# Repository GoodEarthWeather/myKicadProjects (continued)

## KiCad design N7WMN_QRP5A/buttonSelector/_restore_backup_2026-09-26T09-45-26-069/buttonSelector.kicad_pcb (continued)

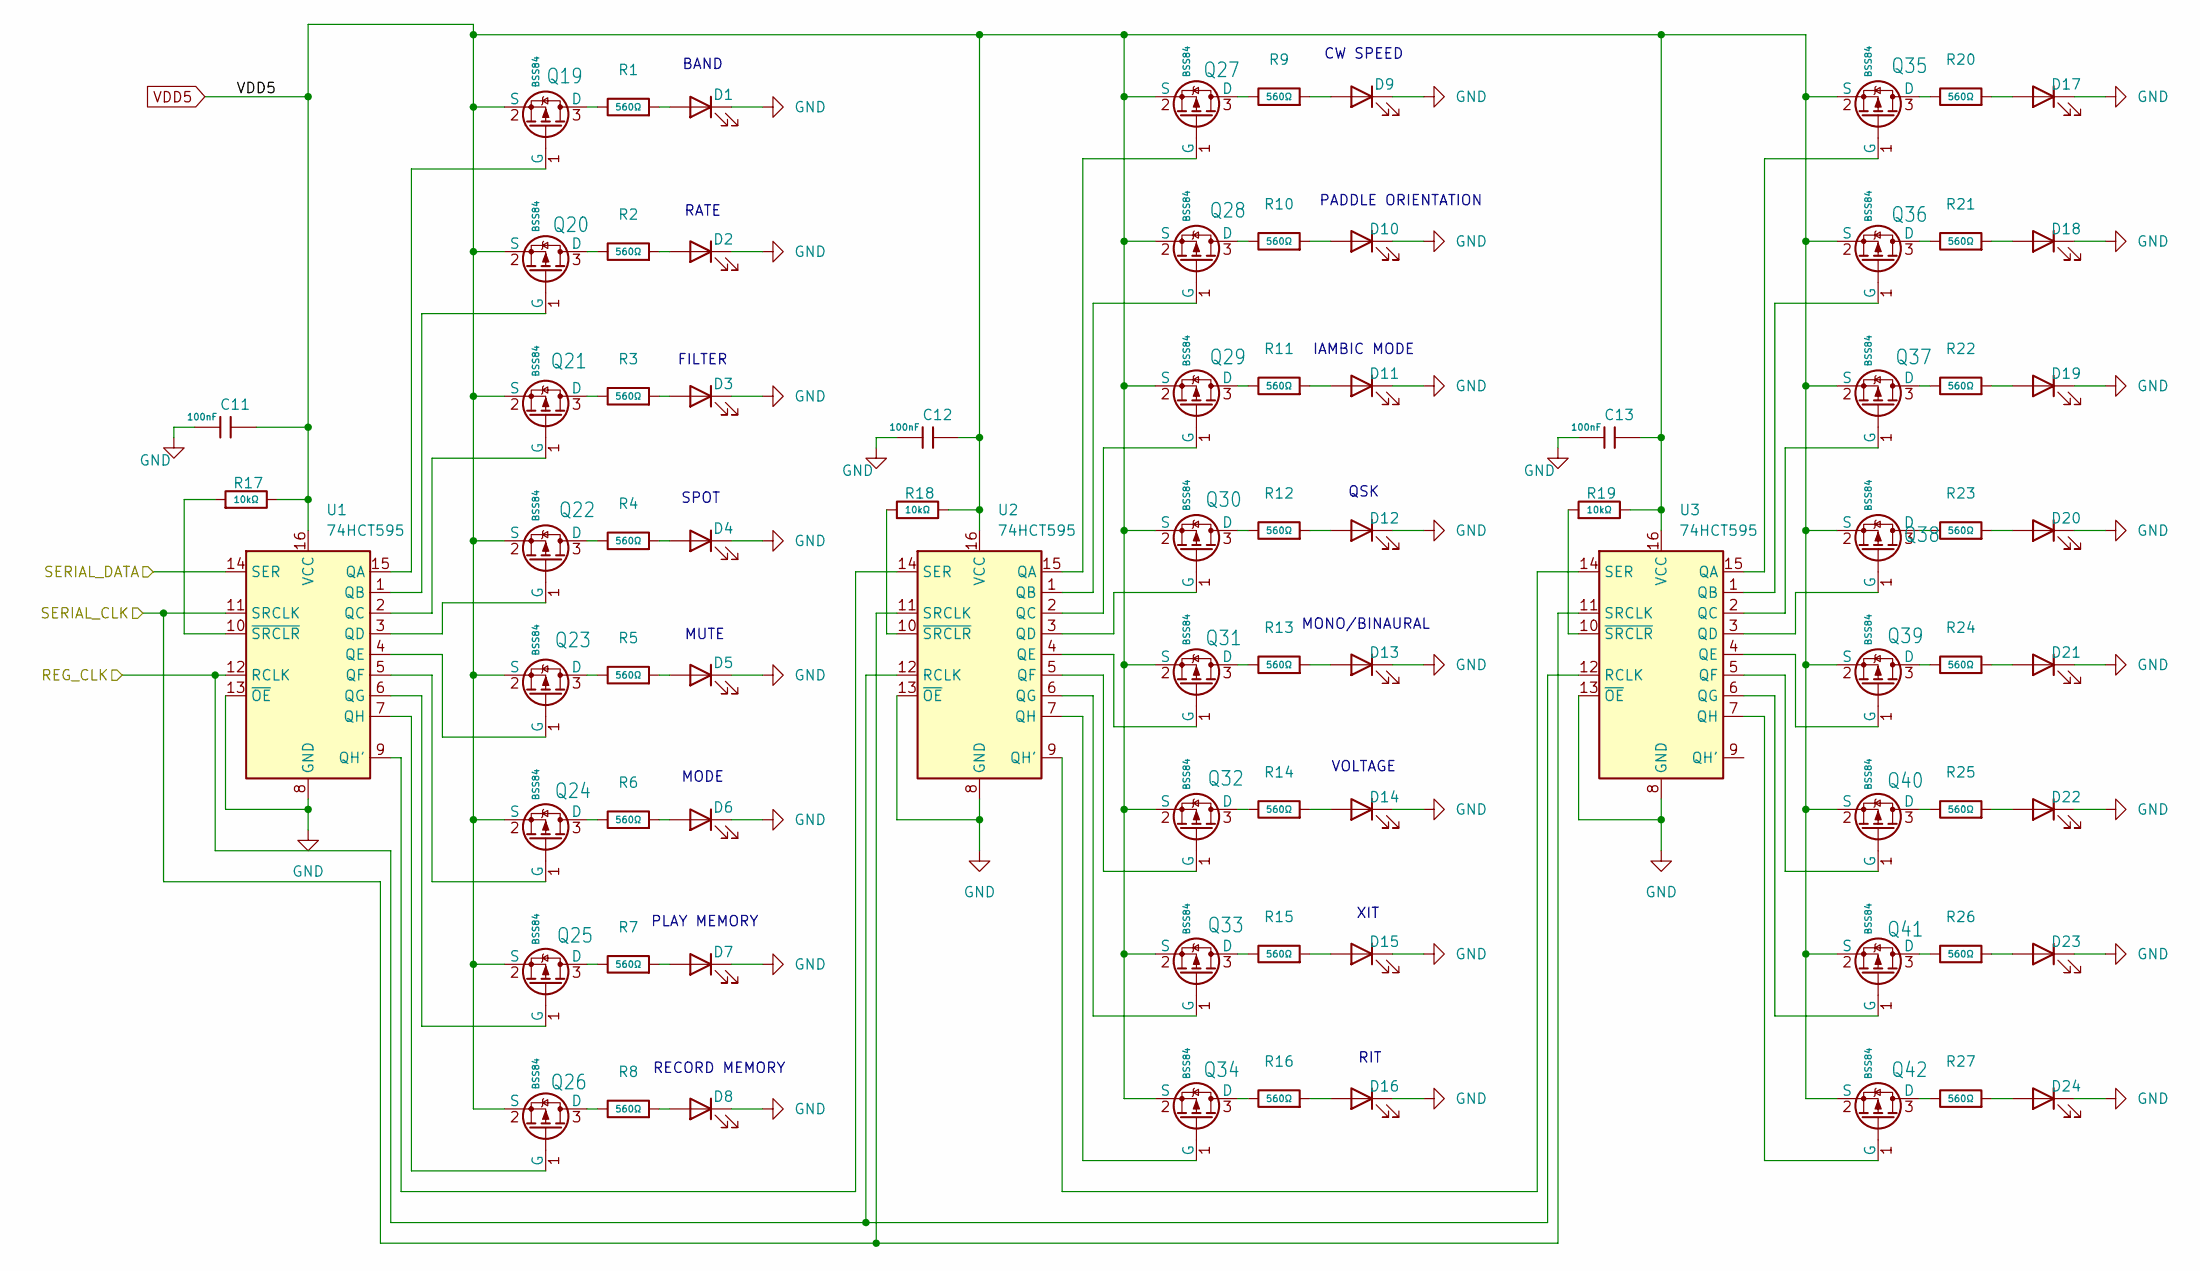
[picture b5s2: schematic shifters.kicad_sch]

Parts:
C11, C12, C13: 100nF; C_0603; Voltage Rated 50V; Tolerance ±10%; Part CC0603KRX7R9BB104; LCSC C14663
D1, D2, D3, D4, D5, D6, D7, D8, D9, D10, D11, D12, D13, D14, D15, D16, D17, D18, D19, D20, D21, D22, D23, D24: LED; LED_D5.0mm_Clear; Mouser Part Number 606-CMD333URC2
Q19, Q20, Q21, Q22, Q23, Q24, Q25, Q26, Q27, Q28, Q29, Q30, Q31, Q32, Q33, Q34, Q35, Q36, Q37, Q38, Q39, Q40, Q41, Q42: BSS84; Q_SOT-23; Part BSS84; JLCPCB C65189
R1, R2, R3, R4, R5, R6, R7, R8, R9, R10, R11, R12, R13, R14, R15, R16, R20, R21, R22, R23, R24, R25, R26, R27: 560Ω; R_0603; Overload Voltage (Max) 75V; Tolerance ±1%; Part 0603WAF5600T5E; JLCPCB C23204
R17, R18, R19: 10kΩ; R_0603; Overload Voltage (Max) 75V; Tolerance ±1%; Part 0603WAF1002T5E; LCSC C25804
U1, U2, U3: 74HCT595; TSSOP-16_4.4x5mm_P0.65mm; JLCPCB C3304571

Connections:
/REG_CLK: U1.12 (RCLK), U2.12 (RCLK), U3.12 (RCLK); also elsewhere on the board
/SERIAL_CLK: U1.11 (SRCLK), U2.11 (SRCLK), U3.11 (SRCLK); also elsewhere on the board
/SERIAL_DATA: U1.14 (SER); also elsewhere on the board
GND: C11.2, C12.2, C13.2, D1.1 (K), D2.1 (K), D3.1 (K), D4.1 (K), D5.1 (K), D6.1 (K), D7.1 (K), D8.1 (K), D9.1 (K), D10.1 (K), D11.1 (K), D12.1 (K), D13.1 (K), D14.1 (K), D15.1 (K), D16.1 (K), D17.1 (K), D18.1 (K), D19.1 (K), D20.1 (K), D21.1 (K), D22.1 (K), D23.1 (K), D24.1 (K), U1.8 (GND), U1.13 (~OE), U2.8 (GND), U2.13 (~OE), U3.8 (GND), U3.13 (~OE); also elsewhere on the board
unnamed: D1.2 (A), R1.1
unnamed: D2.2 (A), R2.1
unnamed: D3.2 (A), R3.1
unnamed: D4.2 (A), R4.1
unnamed: D5.2 (A), R5.1
unnamed: D6.2 (A), R6.1
unnamed: D7.2 (A), R7.1
unnamed: D8.2 (A), R8.1
unnamed: D9.2 (A), R9.1
unnamed: D10.2 (A), R10.1
unnamed: D11.2 (A), R11.1
unnamed: D12.2 (A), R12.1
unnamed: D13.2 (A), R13.1
unnamed: D14.2 (A), R14.1
unnamed: D15.2 (A), R15.1
unnamed: D16.2 (A), R16.1
unnamed: D17.2 (A), R20.1
unnamed: D18.2 (A), R21.1
unnamed: D19.2 (A), R22.1
unnamed: D20.2 (A), R23.1
unnamed: D21.2 (A), R24.1
unnamed: D22.2 (A), R25.1
unnamed: D23.2 (A), R26.1
unnamed: D24.2 (A), R27.1
unnamed: Q19.3 (D), R1.2
unnamed: Q19.1 (G), U1.15 (QA)
unnamed: Q20.3 (D), R2.2
unnamed: Q20.1 (G), U1.1 (QB)
unnamed: Q21.3 (D), R3.2
unnamed: Q21.1 (G), U1.2 (QC)
unnamed: Q22.3 (D), R4.2
unnamed: Q22.1 (G), U1.3 (QD)
unnamed: Q23.3 (D), R5.2
unnamed: Q23.1 (G), U1.4 (QE)
unnamed: Q24.3 (D), R6.2
unnamed: Q24.1 (G), U1.5 (QF)
unnamed: Q25.3 (D), R7.2
unnamed: Q25.1 (G), U1.6 (QG)
unnamed: Q26.3 (D), R8.2
unnamed: Q26.1 (G), U1.7 (QH)
unnamed: Q27.3 (D), R9.2
unnamed: Q27.1 (G), U2.15 (QA)
unnamed: Q28.3 (D), R10.2
unnamed: Q28.1 (G), U2.1 (QB)
unnamed: Q29.3 (D), R11.2
unnamed: Q29.1 (G), U2.2 (QC)
unnamed: Q30.3 (D), R12.2
unnamed: Q30.1 (G), U2.3 (QD)
unnamed: Q31.3 (D), R13.2
unnamed: Q31.1 (G), U2.4 (QE)
unnamed: Q32.3 (D), R14.2
unnamed: Q32.1 (G), U2.5 (QF)
unnamed: Q33.3 (D), R15.2
unnamed: Q33.1 (G), U2.6 (QG)
unnamed: Q34.3 (D), R16.2
unnamed: Q34.1 (G), U2.7 (QH)
unnamed: Q35.3 (D), R20.2
unnamed: Q35.1 (G), U3.15 (QA)
unnamed: Q36.3 (D), R21.2
unnamed: Q36.1 (G), U3.1 (QB)
unnamed: Q37.3 (D), R22.2
unnamed: Q37.1 (G), U3.2 (QC)
unnamed: Q38.3 (D), R23.2
unnamed: Q38.1 (G), U3.3 (QD)
unnamed: Q39.3 (D), R24.2
unnamed: Q39.1 (G), U3.4 (QE)
unnamed: Q40.3 (D), R25.2
unnamed: Q40.1 (G), U3.5 (QF)
unnamed: Q41.3 (D), R26.2
unnamed: Q41.1 (G), U3.6 (QG)
unnamed: Q42.3 (D), R27.2
unnamed: Q42.1 (G), U3.7 (QH)
unnamed: U1.9 (QH'), U2.14 (SER)
unnamed: R17.1, U1.10 (~SRCLR)
unnamed: U2.9 (QH'), U3.14 (SER)
unnamed: R18.1, U2.10 (~SRCLR)
unnamed: R19.1, U3.10 (~SRCLR)
VDD5: C11.1, C12.1, C13.1, Q19.2 (S), Q20.2 (S), Q21.2 (S), Q22.2 (S), Q23.2 (S), Q24.2 (S), Q25.2 (S), Q26.2 (S), Q27.2 (S), Q28.2 (S), Q29.2 (S), Q30.2 (S), Q31.2 (S), Q32.2 (S), Q33.2 (S), Q34.2 (S), Q35.2 (S), Q36.2 (S), Q37.2 (S), Q38.2 (S), Q39.2 (S), Q40.2 (S), Q41.2 (S), Q42.2 (S), R17.2, R18.2, R19.2, U1.16 (VCC), U2.16 (VCC), U3.16 (VCC); also elsewhere on the board

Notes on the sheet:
MONO/BINAURAL
PLAY MEMORY
MUTE
QSK
RECORD MEMORY
SPOT
VOLTAGE
FILTER
BAND
RATE
IAMBIC MODE
RIT
MODE
PADDLE ORIENTATION
XIT
CW SPEED

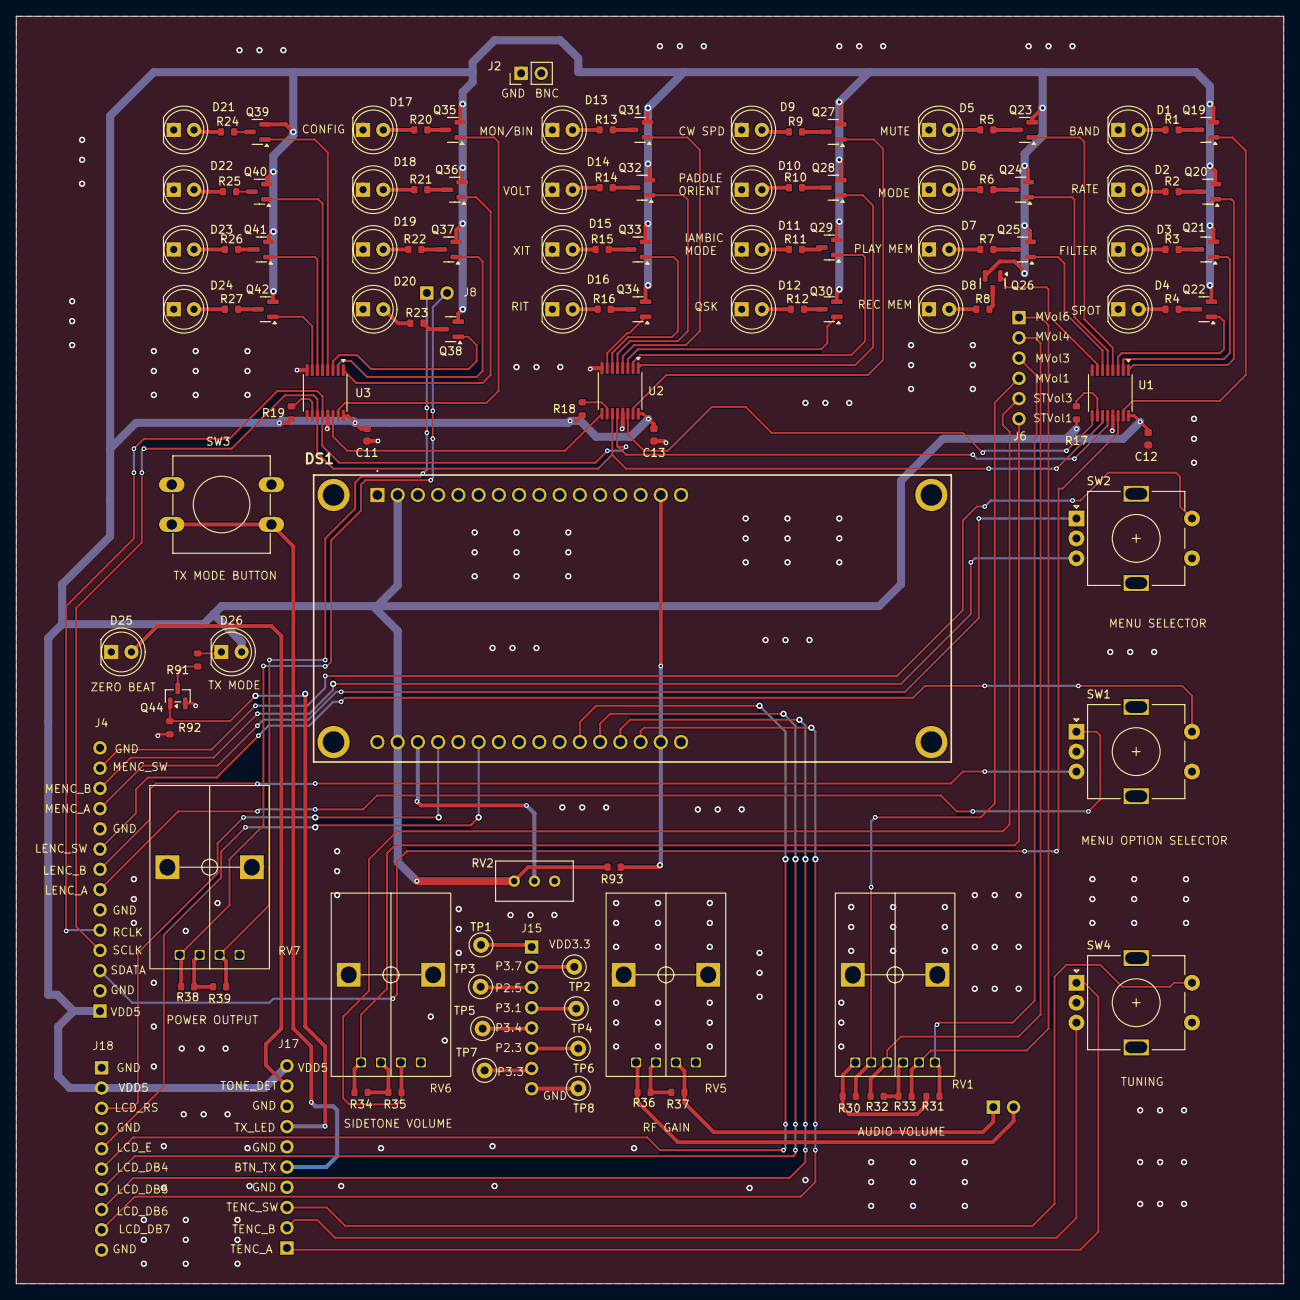
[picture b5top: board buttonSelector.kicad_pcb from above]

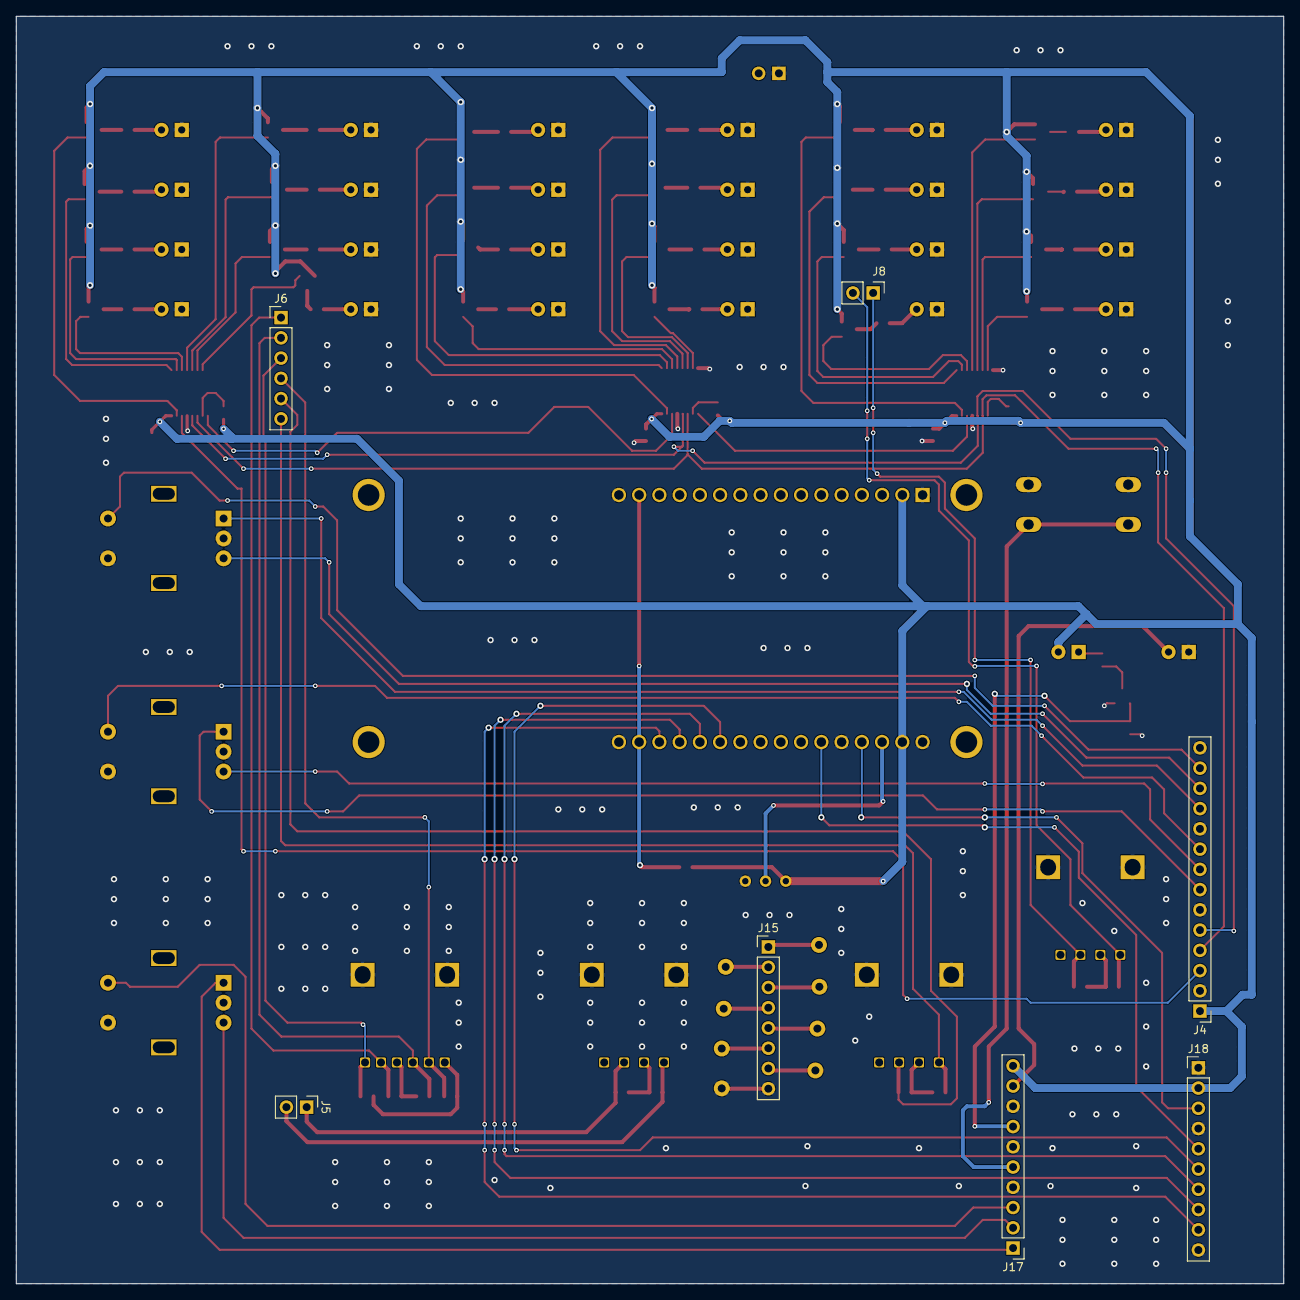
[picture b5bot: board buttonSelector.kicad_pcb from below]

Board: 2 copper layers, 159.0 x 159.0 mm, 123 parts (7 on the bottom side), 126 nets.

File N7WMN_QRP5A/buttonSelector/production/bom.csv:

Designator,Footprint,Quantity,Value,LCSC Part #
"C11, C12, C13",C_0603,3,100nF,C14663
"Q19, Q20, Q21, Q22, Q23, Q24, Q25, Q26, Q27, Q28, Q29, Q30, Q31, Q32, Q33, Q34, Q35, Q36, Q37, Q38, Q39, Q40, Q41, Q42",Q_SOT-23,24,BSS84,C7420340
Q44,SOT-23,1,2N7002,C65189
"R1, R10, R11, R12, R13, R14, R15, R16, R2, R20, R21, R22, R23, R24, R25, R26, R27, R3, R4, R5, R6, R7, R8, R9",R_0603,24,560Ω,C23204
"R17, R18, R19",R_0603,3,10kΩ,C25804
"R30, R31, R32, R33, R34, R35, R36, R37, R38, R39, R93",R_0603,11,0Ω,C21189
R91,R_0603,1,330Ω,C23138
R92,R_0603,1,39kΩ,C23153
"U1, U2, U3",TSSOP-16_4.4x5mm_P0.65mm,3,74HCT595,C3304571

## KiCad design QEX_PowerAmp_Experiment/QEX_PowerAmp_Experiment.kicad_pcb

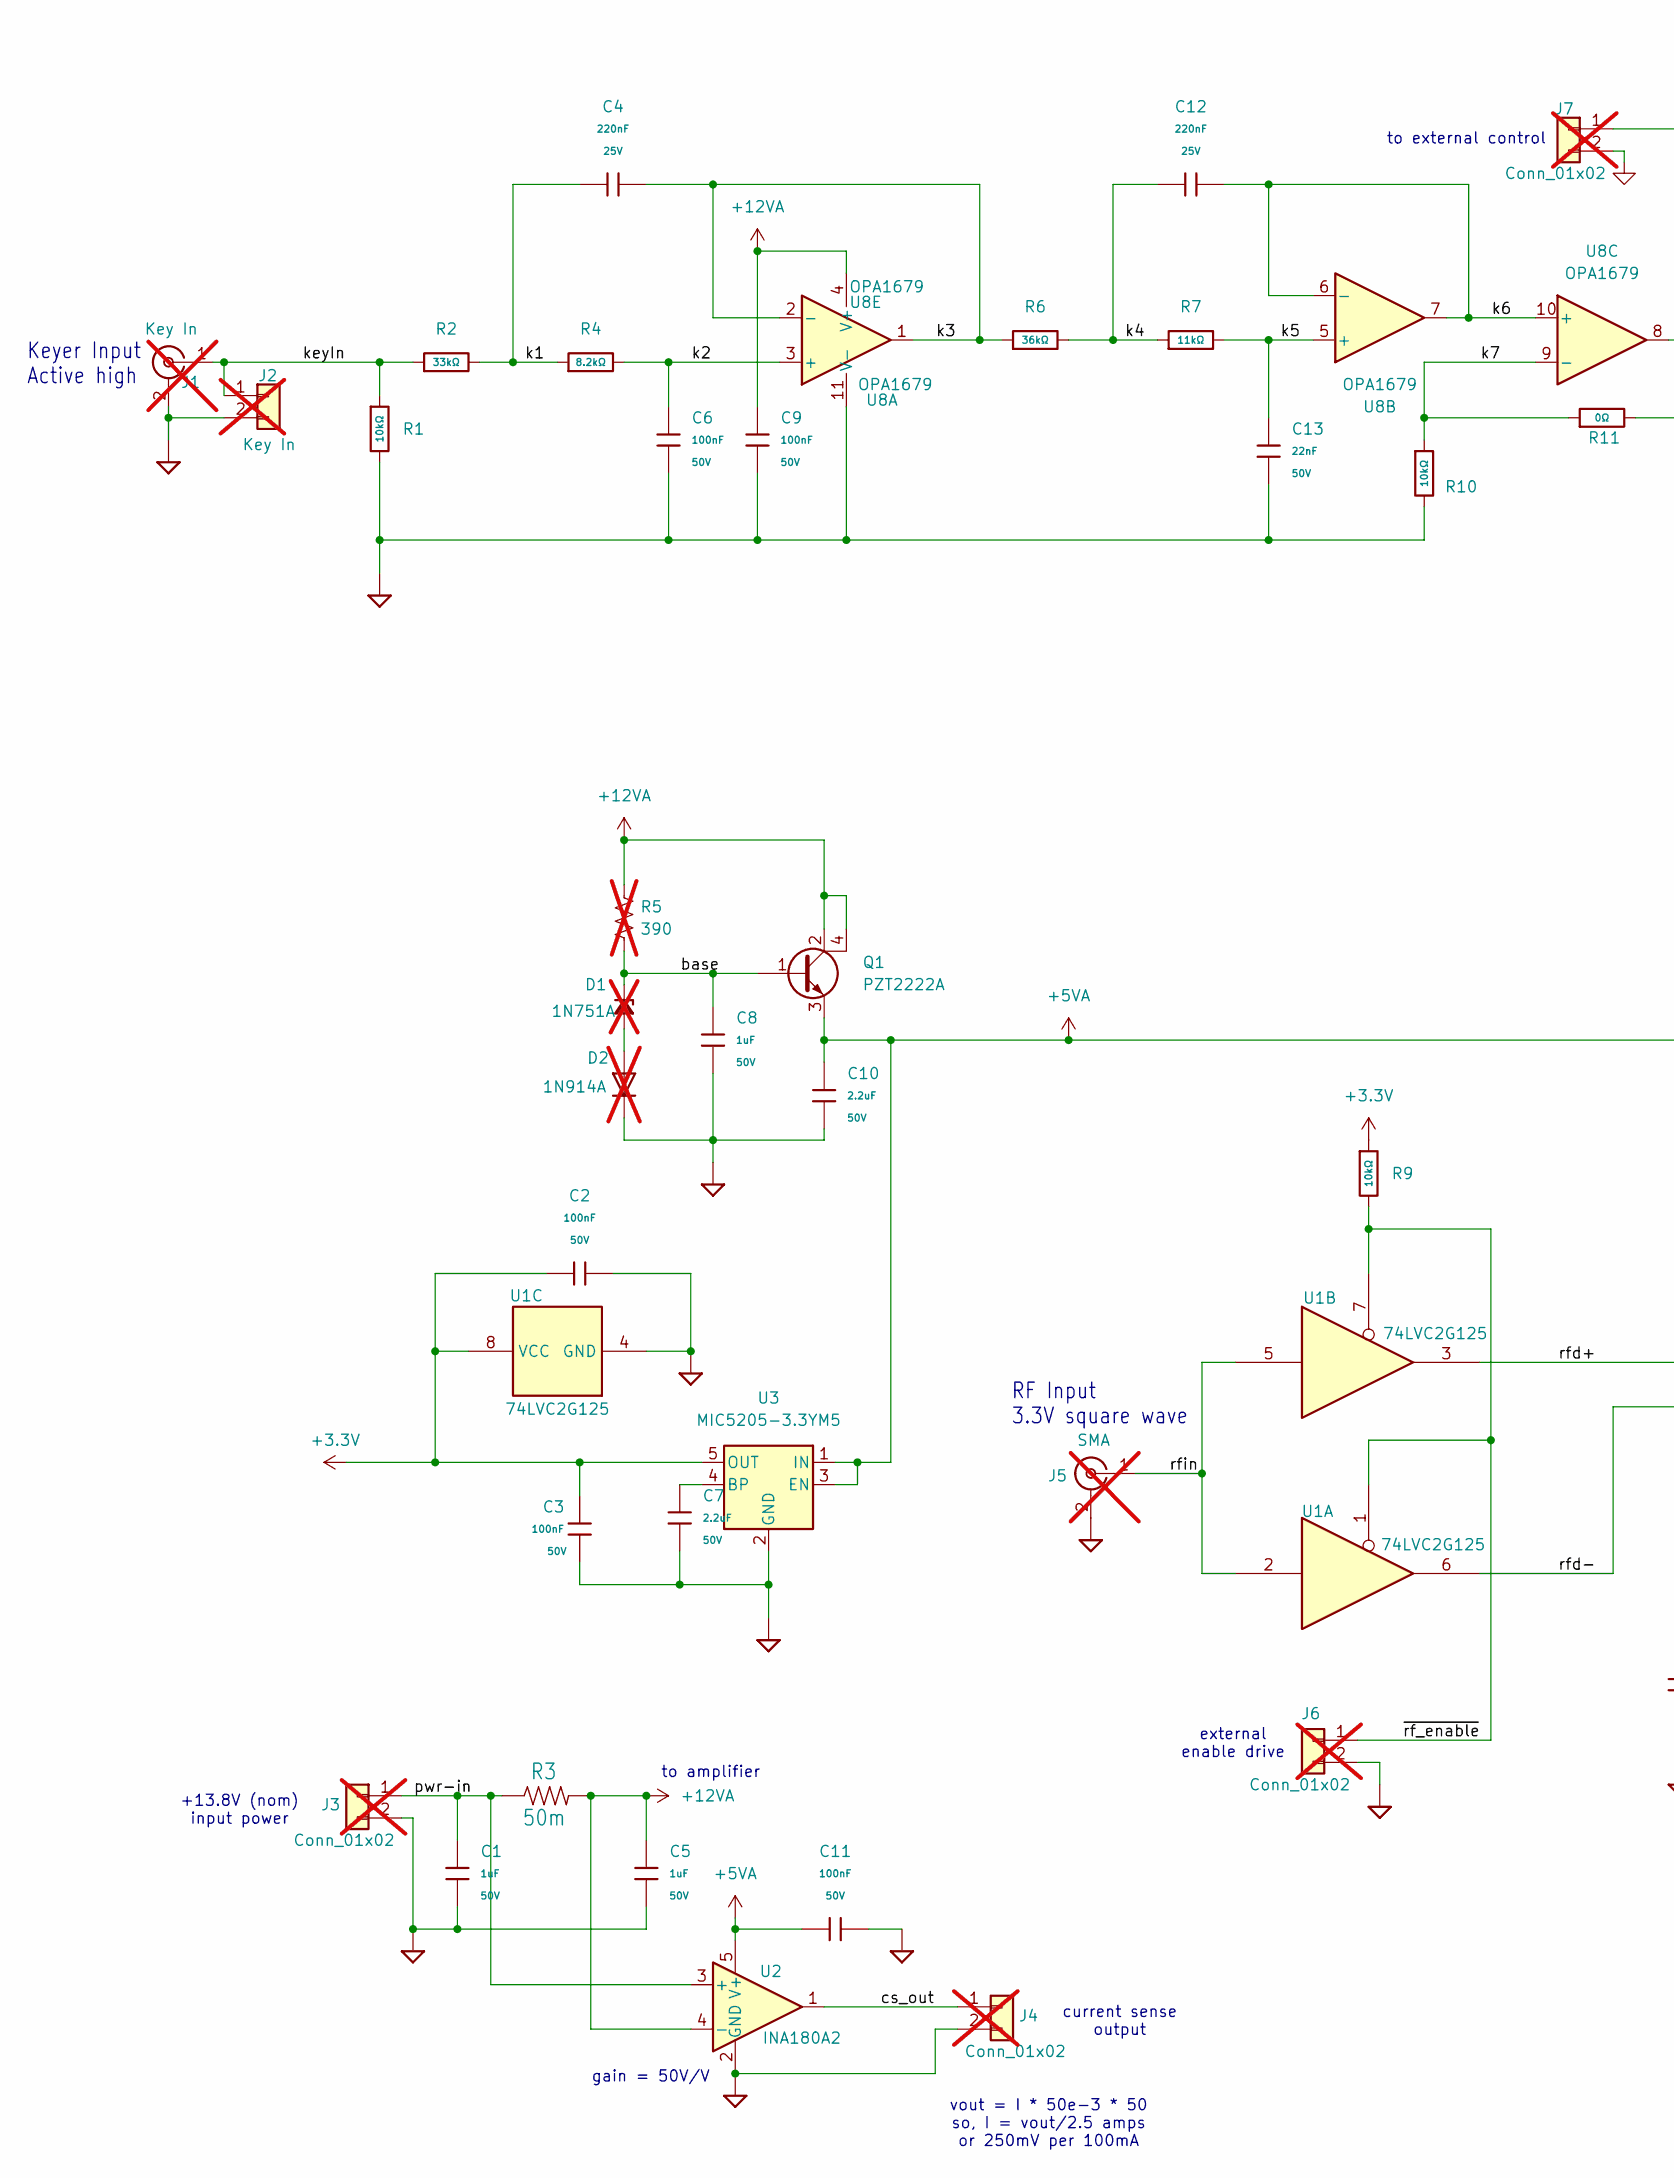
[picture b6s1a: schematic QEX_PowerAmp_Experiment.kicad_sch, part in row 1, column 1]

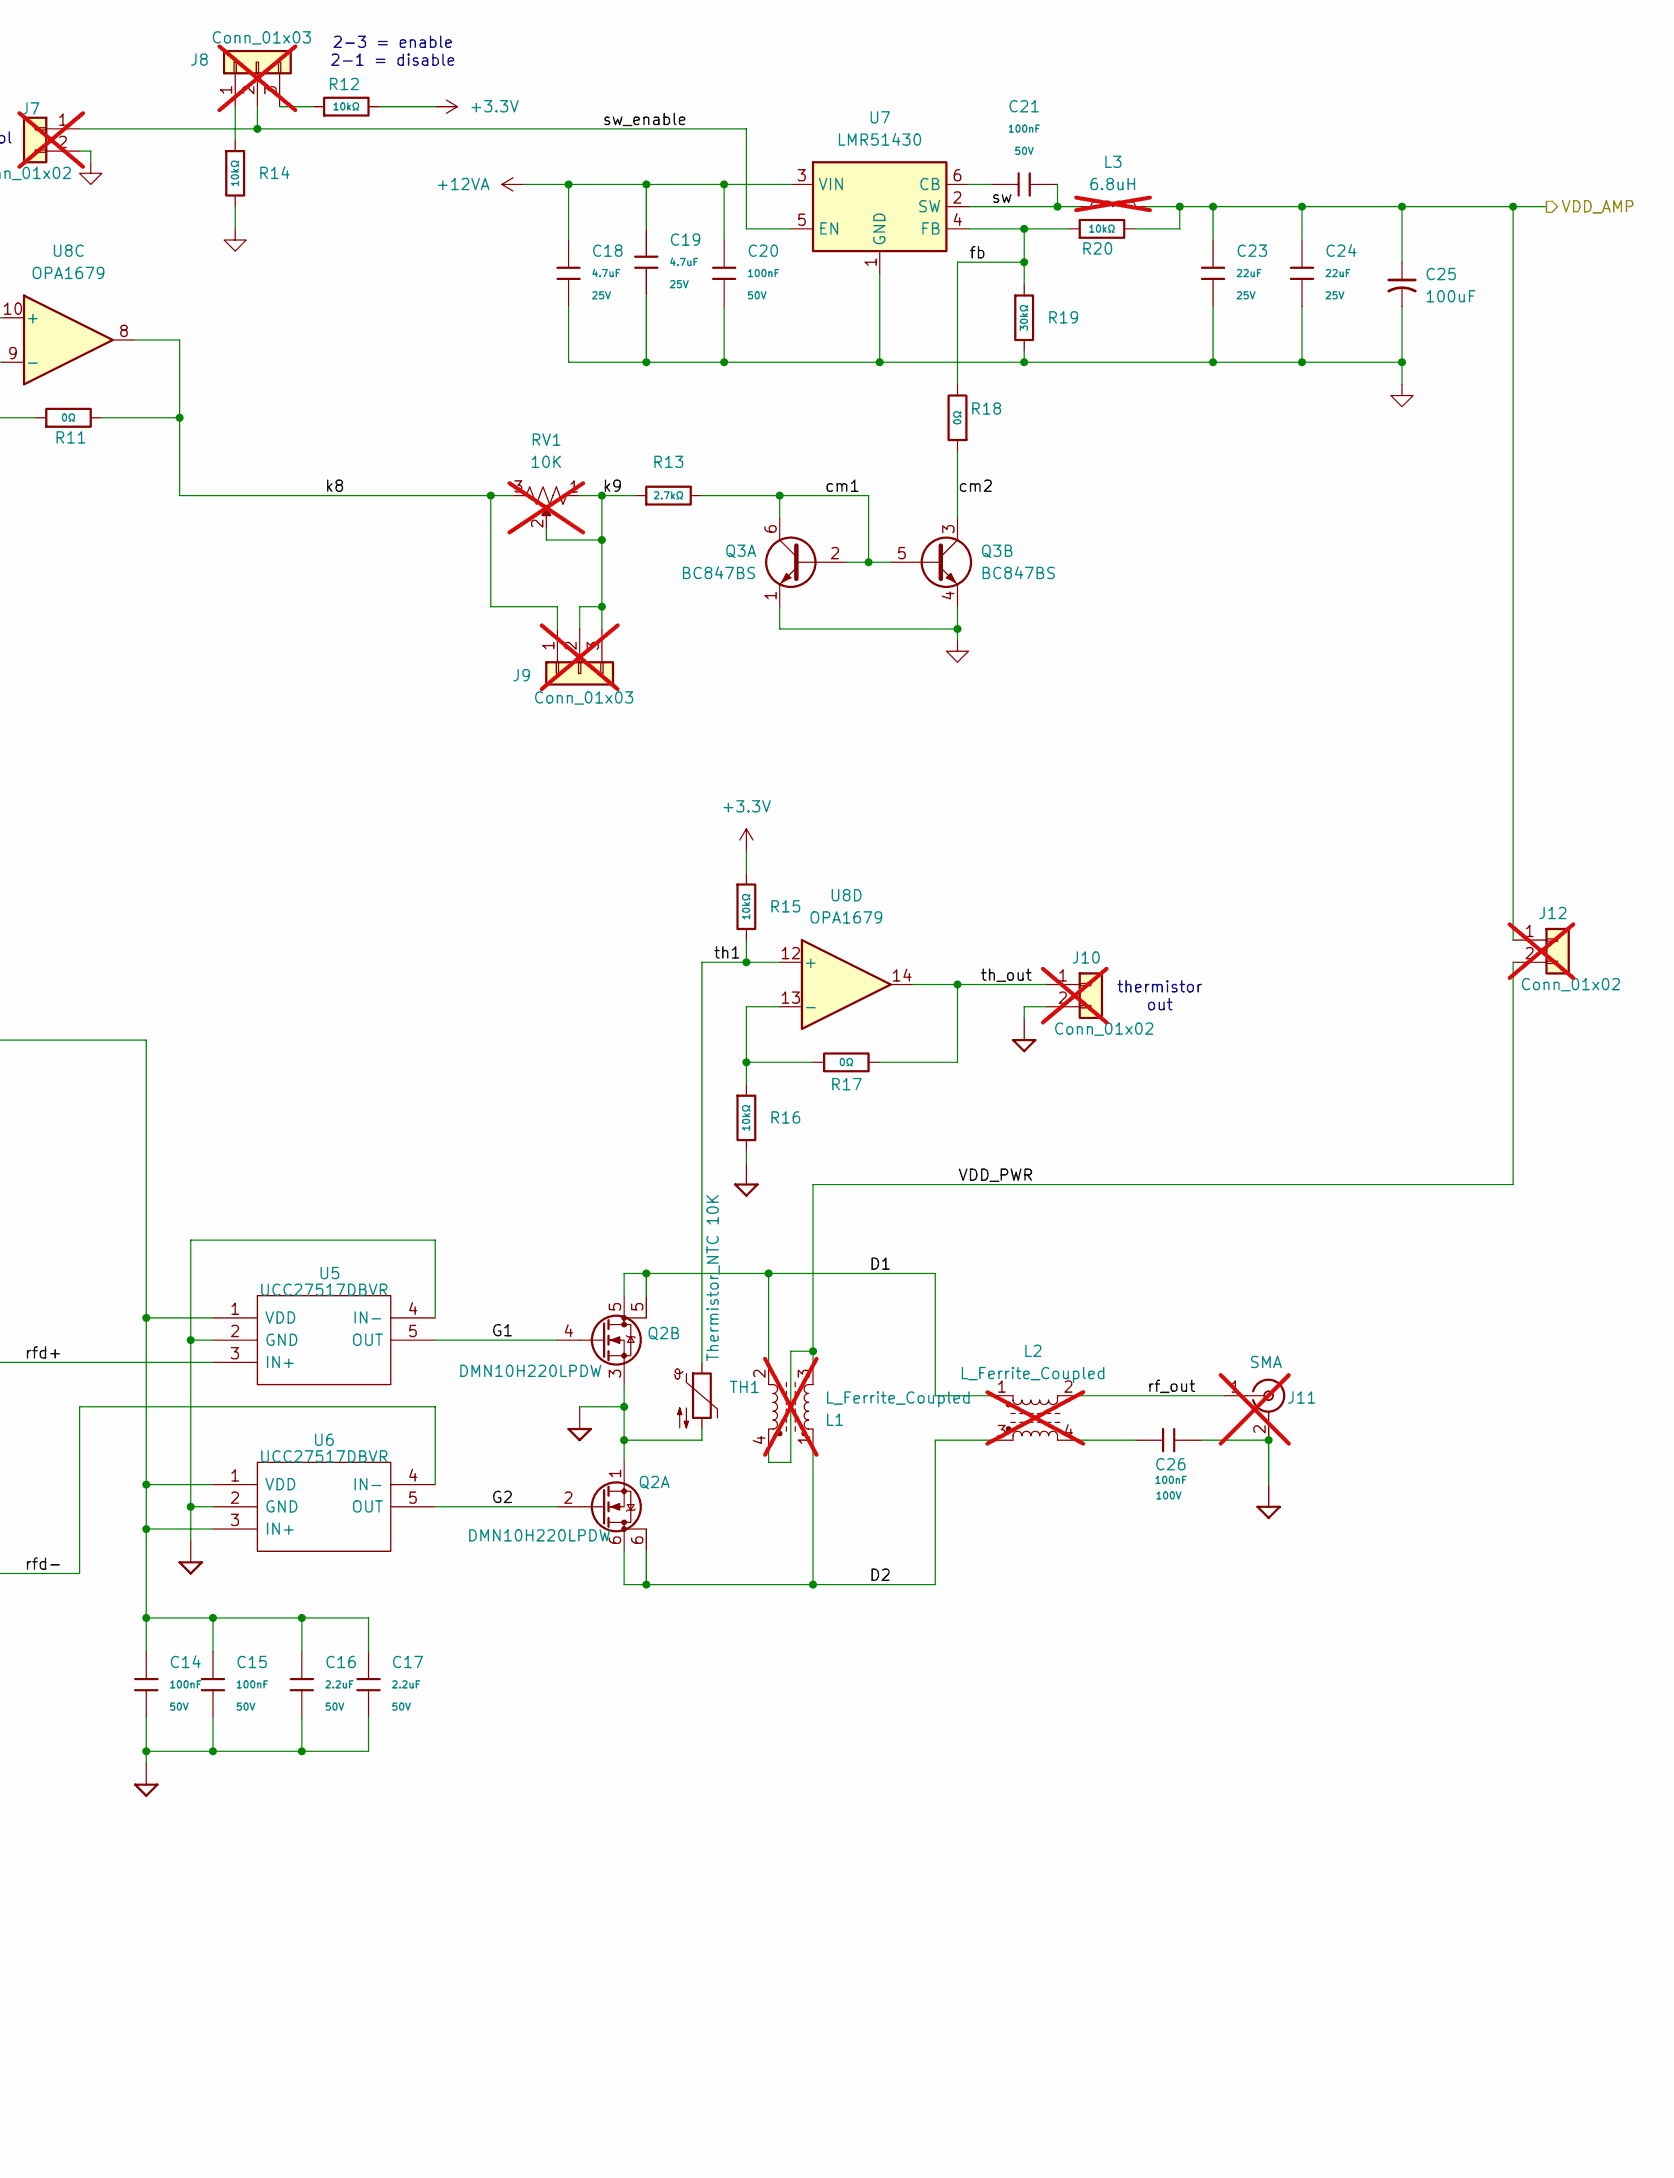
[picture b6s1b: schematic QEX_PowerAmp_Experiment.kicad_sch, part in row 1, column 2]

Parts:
C1, C5, C8: 1uF; C_0603; Voltage Rated 50V; Tolerance ±10%; Part CL10A105KB8NNNC; LCSC C15849
C2, C3, C6, C9, C11, C14, C15, C20, C21: 100nF; C_0603; Voltage Rated 50V; Tolerance ±10%; Part CC0603KRX7R9BB104; LCSC C14663
C4, C12: 220nF; C_0603; Voltage Rated 25V; Tolerance ±10%; Part CL10B224KA8NNNC; LCSC C21120
C7, C10, C16, C17: 2.2uF; C_0805; Voltage Rated 50V; Tolerance ±10%; Part CL21A225KBQNNNE; LCSC C377773
C13: 22nF; C_0603; Voltage Rated 50V; Tolerance ±10%; Part CL10B223KB8NNNC; LCSC C21122
C18, C19: 4.7uF; C_0805; Voltage Rated 25V; Tolerance ±10%; Part CL21A475KAQNNNE; LCSC C1779
C23, C24: 22uF; C_0805; Voltage Rated 25V; Tolerance ±20%; Part CL21A226MAQNNNE; LCSC C45783
C25: 100uF; C_Elec_6.3x5.8; MouserPN 667-EEE-FT1V101AP
C26: 100nF; C_0805; Voltage Rated 100V; Tolerance ±10%; Part CL21B104KCFNNNE; LCSC C28233
D1: 1N751A; D_DO-35_SOD27_P7.62mm_Horizontal; MouserPN 1N751A TR PBFREE; not fitted
D2: 1N914A; D_DO-35_SOD27_P7.62mm_Horizontal; MouserPN 512-1N914ATR; not fitted
J1: Key In; SMA_Molex_73251-1153_EdgeMount_Horizontal; not fitted
J2: Key In; PinHeader_1x02_P2.54mm_Vertical; not fitted
J3, J4, J6, J7, J10, J12: Conn_01x02; PinHeader_1x02_P2.54mm_Vertical; not fitted
J5, J11: SMA; SMA_Molex_73251-1153_EdgeMount_Horizontal; not fitted
J8, J9: Conn_01x03; PinHeader_1x03_P2.54mm_Vertical; not fitted
L1, L2: L_Ferrite_Coupled; Transformer_Toroid_Horizontal_D14.0mm_Amidon-T50; not fitted
L3: 6.8uH; L_10.4x10.4_H4.8; MouserPN 710-7447714068; not fitted
Q1: PZT2222A; SOT-223; MouserPN 771-PZT2222A115
Q2: DMN10H220LPDW; DMN10H220LPDW13; MouserPN 621-DMN10H220LPDW-13
Q3: BC847BS; SOT-363_SC-70-6; Part BC847BS; LCSC C41375126
R1, R9, R10, R12, R14, R15, R16, R20: 10kΩ; R_0603; Overload Voltage (Max) 75V; Tolerance ±1%; Part 0603WAF1002T5E; LCSC C25804
R2: 33kΩ; R_0603; Overload Voltage (Max) 75V; Tolerance ±1%; Part 0603WAF3302T5E; LCSC C4216
R3: 50m; R_0805_2012Metric_Pad1.20x1.40mm_HandSolder; MouserPN 667-ERJ-6BWFR050V
R4: 8.2kΩ; R_0603; Overload Voltage (Max) 75V; Tolerance ±1%; Part 0603WAF8201T5E; LCSC C25981
R5: 390; R_Axial_DIN0207_L6.3mm_D2.5mm_P10.16mm_Horizontal; not fitted
R6: 36kΩ; R_0603; Overload Voltage (Max) 75V; Tolerance ±1%; Part 0603WAF3602T5E; LCSC C23147
R7: 11kΩ; R_0603; Overload Voltage (Max) 75V; Tolerance ±1%; Part 0603WAF1102T5E; LCSC C25950
R11, R17, R18: 0Ω; R_0603; Overload Voltage (Max) 75V; Tolerance ±1%; Part 0603WAF0000T5E; LCSC C21189
R13: 2.7kΩ; R_0603; Overload Voltage (Max) 75V; Tolerance ±1%; Part 0603WAF2701T5E; LCSC C13167
R19: 30kΩ; R_0603; Overload Voltage (Max) 75V; Tolerance ±1%; Part 0603WAF3002T5E; LCSC C22984
RV1: 10K; Potentiometer_Bourns_3296W_Vertical; not fitted
TH1: Thermistor_NTC 10K; R_0603; MouserPN 594-NTCS0603E3103GMT; Mouser 594-NTCS0603E3103GMT
U1: 74LVC2G125; SSOP-8_2.95x2.8mm_P0.65mm; MouserPN 595-74LVC2G125DCTRE4
U2: INA180A2; SOT-23-5; LCSC C192764
U3: MIC5205-3.3YM5; SOT-23-5_HandSoldering; MouserPN 998-MIC5205-3.3YM5TR
U5, U6: UCC27517DBVR; SOT-23-5_HandSoldering; Mouser Part Number 595-UCC27517DBVR
U7: LMR51430; SOT-23-6; LCSC C5185863
U8: OPA1679; SOIC-14_3.9x8.7mm_P1.27mm; LCSC C2878631

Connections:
+3.3V: C2.1, C3.1, R9.1, R12.2, R15.1, U1.8 (VCC), U3.5 (OUT)
+5VA: C10.1, C11.1, C14.1, C15.1, C16.1, C17.1, Q1.3 (E), U2.5 (V+), U3.1 (IN), U3.3 (EN), U5.1 (VDD), U6.1 (VDD), U6.3 (IN+)
+12VA: C5.1, C9.1, C18.1, C19.1, C20.1, Q1.2 (C), Q1.4 (C), R3.2, R5.1, U2.4 (-), U7.3 (VIN), U8.4 (V+)
/D1: L1.2, L2.1, Q2.5 (D)
/D2: L1.1, L2.3, Q2.6 (D)
/G1: Q2.4 (G), U5.5 (OUT)
/G2: Q2.2 (G), U6.5 (OUT)
/VDD_AMP: C23.1, C24.1, C25.1, J12.1, L3.2, R20.2
/VDD_PWR: J12.2, L1.3, L1.4
/base: C8.1, D1.1 (K), Q1.1 (B), R5.2
/cm1: Q3.2 (B1), Q3.5 (B2), Q3.6 (C1), R13.2
/cm2: Q3.3 (C2), R18.1
/cs_out: J4.1, U2.1
/fb: R18.2, R19.1, R20.1, U7.4 (FB)
/k1: C4.1, R2.2, R4.1
/k2: C6.1, R4.2, U8.3 (+)
/k3: C4.2, R6.1, U8.1, U8.2 (-)
/k4: C12.1, R6.2, R7.1
/k5: C13.1, R7.2, U8.5 (+)
/k6: C12.2, U8.6 (-), U8.7, U8.10 (+)
/k7: R10.1, R11.1, U8.9 (-)
/k8: J9.1, R11.2, RV1.3, U8.8
/k9: J9.2, J9.3, R13.1, RV1.1, RV1.2
/keyIn: J1.1 (In), J2.1, R1.1, R2.1
/pwr-in: C1.1, J3.1, R3.1, U2.3 (+)
/rf_out: J11.1 (In), L2.2
/rfd+: U1.3, U5.3 (IN+)
/rfd-: U1.6, U6.4 (IN-)
/rfin: J5.1 (In), U1.2, U1.5
/sw: C21.2, L3.1, U7.2 (SW)
/sw_enable: J7.1, J8.2, U7.5 (EN)
/th1: R15.2, TH1.1, U8.12 (+)
/th_out: J10.1, R17.2, U8.14
/~rf_enable: J6.1, R9.2, U1.1, U1.7
GND: C1.2, C2.2, C3.2, C5.2, C6.2, C7.2, C8.2, C9.2, C10.2, C11.2, C13.2, C14.2, C15.2, C16.2, C17.2, C18.2, C19.2, C20.2, C23.2, C24.2, C25.2, C26.2, D2.1 (K), J1.2 (Ext), J2.2, J3.2, J4.2, J5.2 (Ext), J6.2, J7.2, J10.2, J11.2 (Ext), Q2.1 (S), Q2.3 (S), Q3.1 (E1), Q3.4 (E2), R1.2, R10.2, R14.2, R16.2, R19.2, TH1.2, U1.4 (GND), U2.2 (GND), U3.2 (GND), U5.2 (GND), U5.4 (IN-), U6.2 (GND), U7.1 (GND), U8.11 (V-)
unnamed: C26.1, L2.4
unnamed: D1.2 (A), D2.2 (A)
unnamed: J8.1, R14.1
unnamed: J8.3, R12.1
unnamed: C7.1, U3.4 (BP)
unnamed: C21.1, U7.6 (CB)
unnamed: R16.1, R17.1, U8.13 (-)

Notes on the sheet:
to external control
vout = I * 50e-3 * 50 so, I = vout/2.5 amps or 250mV per 100mA
external enable drive
current sense output
+13.8V (nom) input power
to amplifier
thermistor out
RF Input 3.3V square wave
2-3 = enable 2-1 = disable
Keyer Input Active high
gain = 50V/V

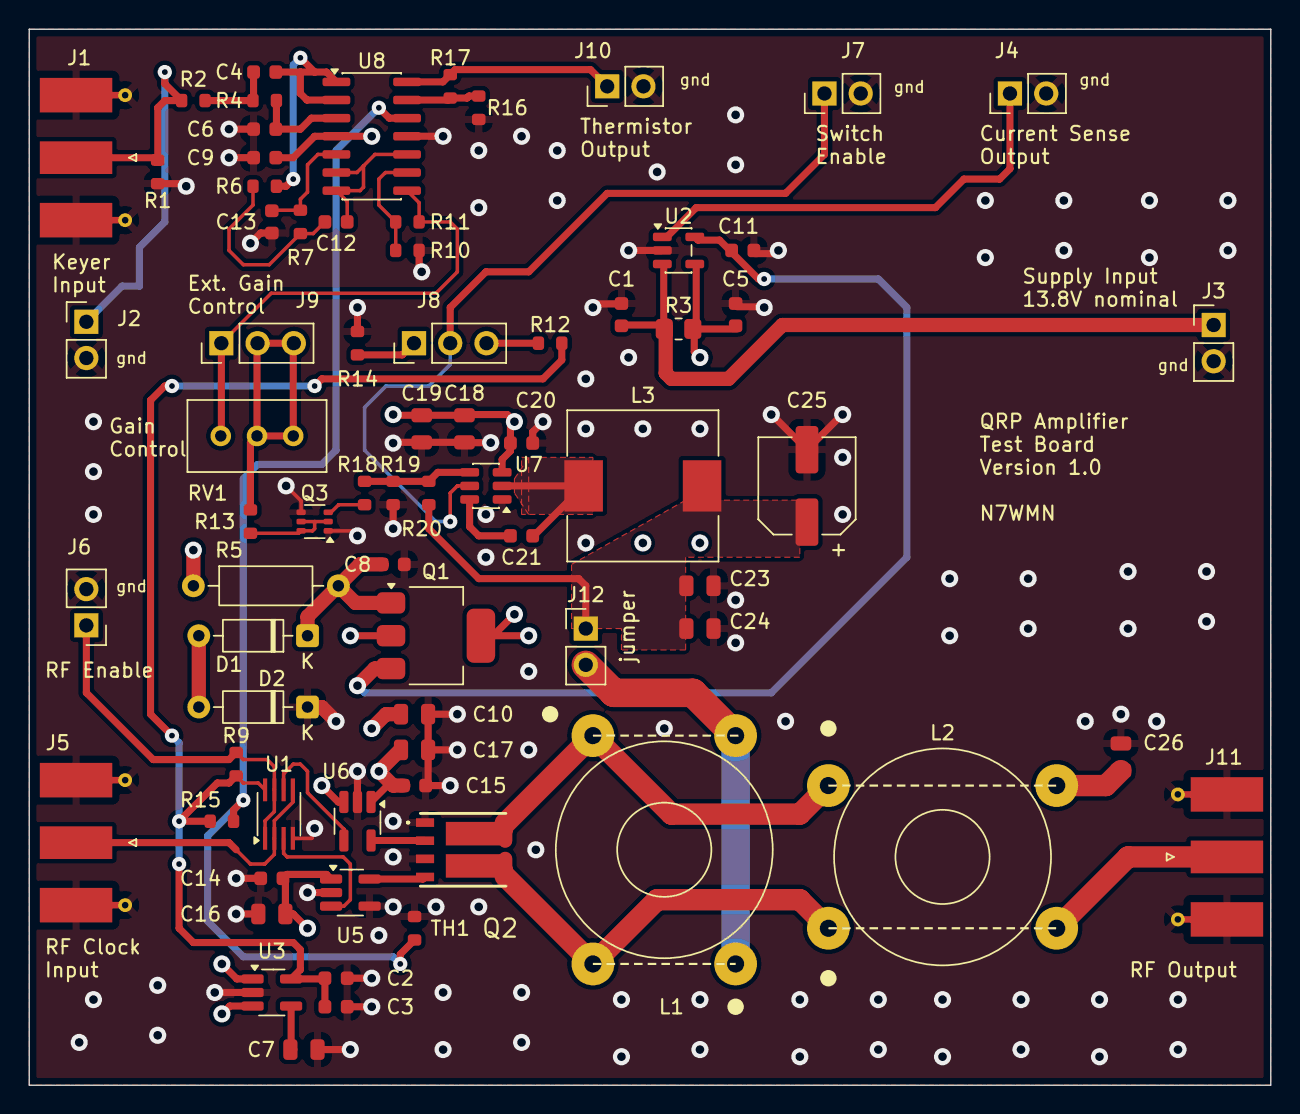
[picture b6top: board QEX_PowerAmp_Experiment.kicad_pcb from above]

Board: 4 copper layers, 87.0 x 74.0 mm, 73 parts (0 on the bottom side), 42 nets.

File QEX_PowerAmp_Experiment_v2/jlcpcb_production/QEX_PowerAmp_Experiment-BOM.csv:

Reference,Value,DNP,Exclude from BOM,Exclude from Board,Footprint,LCSC
RV1,10K,DNP,Excluded from BOM,,Potentiometer_THT:Potentiometer_Bourns_3296W_Vertical,
R5,390,DNP,Excluded from BOM,,Resistor_THT:R_Axial_DIN0207_L6.3mm_D2.5mm_P10.16mm_Horizontal,
L3,6.8uH,DNP,Excluded from BOM,,Inductor_SMD:L_10.4x10.4_H4.8,
"L1,L2",L_Ferrite_Coupled,DNP,Excluded from BOM,,Transformer_THT:Transformer_Toroid_Horizontal_D14.0mm_Amidon-T50,
"J8,J9",Conn_01x03,DNP,Excluded from BOM,,Connector_PinHeader_2.54mm:PinHeader_1x03_P2.54mm_Vertical,
"J5,J11",SMA,DNP,Excluded from BOM,,Connector_Coaxial:SMA_Molex_73251-1153_EdgeMount_Horizontal,
"J3,J4,J6,J7,J10,J12",Conn_01x02,DNP,Excluded from BOM,,Connector_PinHeader_2.54mm:PinHeader_1x02_P2.54mm_Vertical,
J2,Key In,DNP,Excluded from BOM,,Connector_PinHeader_2.54mm:PinHeader_1x02_P2.54mm_Vertical,
J1,Key In,DNP,Excluded from BOM,,Connector_Coaxial:SMA_Molex_73251-1153_EdgeMount_Horizontal,
D2,1N914A,DNP,Excluded from BOM,,Diode_THT:D_DO-35_SOD27_P7.62mm_Horizontal,
D1,1N751A,DNP,Excluded from BOM,,Diode_THT:D_DO-35_SOD27_P7.62mm_Horizontal,
U8,OPA1679,,,,Package_SO:SOIC-14_3.9x8.7mm_P1.27mm,C2878631
U7,LMR51430,,,,Package_TO_SOT_SMD:SOT-23-6,C5185863
"U5,U6",UCC27517DBVR,,,,Package_TO_SOT_SMD:SOT-23-5_HandSoldering,C99395
U3,MIC5205-3.3YM5,,,,Package_TO_SOT_SMD:SOT-23-5_HandSoldering,C37970
U2,INA180A2,,,,Package_TO_SOT_SMD:SOT-23-5,C192764
U1,74LVC2G125,,,,Package_SO:SSOP-8_2.95x2.8mm_P0.65mm,C2675807
TH1,Thermistor_NTC 10K,,,,PCM_JLCPCB:R_0603,
R19,30kΩ,,,,PCM_JLCPCB:R_0603,C22984
R13,2.7kΩ,,,,PCM_JLCPCB:R_0603,C13167
"R11,R17,R18",0Ω,,,,PCM_JLCPCB:R_0603,C21189
R7,11kΩ,,,,PCM_JLCPCB:R_0603,C25950
R6,36kΩ,,,,PCM_JLCPCB:R_0603,C23147
R4,8.2kΩ,,,,PCM_JLCPCB:R_0603,C25981
R3,50m,,,,Resistor_SMD:R_0805_2012Metric_Pad1.20x1.40mm_HandSolder,C858613
R2,33kΩ,,,,PCM_JLCPCB:R_0603,C4216
"R1,R9,R10,R12,R14,R15,R16,R20",10kΩ,,,,PCM_JLCPCB:R_0603,C25804
Q3,BC847BS,,,,PCM_JLCPCB:SOT-363_SC-70-6,C41375126
Q2,DMN10H220LPDW,,,,diodesInc:DMN10H220LPDW13,
Q1,PZT2222A,,,,Package_TO_SOT_SMD:SOT-223,C115272
C26,100nF,,,,PCM_JLCPCB:C_0805,C28233
C25,100uF,,,,Capacitor_SMD:C_Elec_6.3x5.8,C7469933
"C23,C24",22uF,,,,PCM_JLCPCB:C_0805,C45783
"C18,C19",4.7uF,,,,PCM_JLCPCB:C_0805,C1779
C13,22nF,,,,PCM_JLCPCB:C_0603,C21122
"C7,C10,C16,C17",2.2uF,,,,PCM_JLCPCB:C_0805,C377773
"C4,C12",220nF,,,,PCM_JLCPCB:C_0603,C21120
"C2,C3,C6,C9,C11,C14,C15,C20,C21",100nF,,,,PCM_JLCPCB:C_0603,C14663
"C1,C5,C8",1uF,,,,PCM_JLCPCB:C_0603,C15849
